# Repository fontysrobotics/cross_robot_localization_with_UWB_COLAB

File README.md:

# cross_robot_localization_with_UWB_COLAB

The new way to design large scale automation project is through the use of Autonomously Guided Vehicles (AGVs). They allow the connection of different workcells to have more flexibility and all this autonomously. This new technology brings a brandd new market with different companies competing to manufacture the best robot for a said application. This brings the costumers to a place where they have to go to different suppliers for the best AGVs based on their application. Incorporating AGVSs of different brands in the same automation process is a difficult task. While AGVs are good at navigating around a building and completing repetitive tasks, when faced with an unknown moving object such as another AGV they get into trouble. As the different brands cannot communicate this creates a serious issue.

## Project

The goal of the project is to make collaboration between AGVs of different brands possible using a relatively cheap solution. The main issue with collaboration is the lack of communication of crucial data. As the issue arises for navigation, the most important data to be shared between the AGVs is location. Localizing multi-vendor AGVs and sharing their location on the same delocalised system. This will allow the recognition of AGVs as obstacles and will leave room for future implementation of a task division control system. This delocalised communication system will achieve collaboration between the AGVs of various brands.

## Problem

The problem of the assignment is to create a delocalised communication system between the AGVs that can determine the position of each AGV. The localization system is built on the decawave UWB device. The principle of this device is to use the delay in Ultra Wide Band signals to measure distance between the devices on the same network. This localization system must be integrated with the AGVs. Each AGV must have a UWB device for localization which in some way has to be connected to a network of all other AGVs. The creation of this system is the problem of the assignment.

## Solution

In order to incorporate the UWB localization system with the AGV, a device titled Communication and Localization Add on Board or CoLAB was created as a solution. The CoLAB device handles the creation and connection of an AGV to the localization network as well as to the UWB network and the AGV. A CoLAB device is attached to each AGV along with two UWB devices that serve as a front and back tag for the positioning. Inside the CoLAb is a Raspberry pi that reads the positioning information from the two tags via UART. This information is processed to return location and orientation. The CoLAB publishes location, orientation and other useful information from the AGV config file as a message to a network which all AGVs are connected to. From this network AGVs scan and read messages of other AGVs and determine their location orientation and most important properties. This information is sent to the AGV and can be implemented for the software to recognize other AGVs as obstacles. Thus, solving the Communication and Localization issue between AGVs of different vendors. This system also opens the possibility to many more future solutions.

## Navigation of gitHub Page

Within the following the contents of the CoLAB gitHub page will be explained. The three main components the read me, repository and wiki will be highlighted.

* ### Read Me 
Within the read me the basic introduction to the project and problem happens. The products of the project thus to content of the gitHub page is also explained. Alongside this information the main credits to the page as well as a quick how to use guide can be found.

* ### Repository
The repository is where the final products of the project thus the content can be found. This is where the final designs and software can be downloaded from. All the research material used is also provided alongside the datasheets and explaining flow charts and diagrams. Some files to aid with system set up can also be found in the repository.

* ### Wiki
The wiki is where the design is given a further explanation. Each components of the system is given a page along with explanations to its design. Some pages elaborate on the system, validation or final conclusions. For navigation use the table of contents side bar on the right side of the page.

## How to use

Within the following a quick start guide will be given on how to set up the CoLAB system on your own AGV. It is Important to note that this guide will give a global layout and reference set up files, however some extra more in depth set up information might be found in the referenced files.

* ### How to initiate (loading code + connect)
In order to set up a system like the CoLAB first order all the components, print the parts and PCB. After this is completed there is a guide titled (start guide) in the depositor that is an assembly guide to the CoLAB. In this guide further information details how to set up a raspberry pi for the CoLAB as well.
Once the CoLAB is set up it is time to set up the UWB devices with the correct image. Only the tags on the AGV have to be set up

* ### How to set up (config)
It is very easy to use a CoLAB device. It is almost plug and play. There are a couple of things that need to be commpleted before use. A list of these can be found below. It is important to note that these steps must be repeated for each CoLAB device on each AGV.

1. Order all parts and assemble the device compoennets using the [guides](https://github.com/fontysrobotics/cross_robot_localization_with_UWB_COLAB/tree/main/PhysicalSystem/Assembly_documents)
1. Fill out [Configuration File](https://github.com/fontysrobotics/cross_robot_localization_with_UWB_COLAB/blob/main/Software/CoLAB_config.py) of AGV
1. Plug tags to CoLAB and Attach to AGV
1. Note down distance between tags in config file
1. Set up ports of tags using [set up guide](https://github.com/fontysrobotics/cross_robot_localization_with_UWB_COLAB/blob/main/UWB_Documentation/UWB_Setup_Guides/Use%20RaspberryPi%20terminal%20(1).docx)
1. The device must be connected to the network and it is ready to use

* ### End results
As an end reslut of running the code correctly, there are two important aspects taht happen. The communication code between all the connected AGVs is running and they are communicating their information to each other. The second thing is a visualziation software that is built into every AGV. This shows the AGVs around. This is the end result of code in a nutshell, the wiki explains further information of the exact communication and information passing through.

## Bibliography & Credits

This project was created as part of a Mechatronics university course for Fontys University of Applied Sciences with the involvement of the following parties:

### Created by
* Nicole Celine
* Arjan van der Heijden
* Mike Luiken
* Simeon Stoyanov
* Pascal Dinjens
* Long Nguyen
* Ryan Muhammad
* Benedek Papp

### Mentorship and Project Ownership
* Pablo Negrete Rubio
* Sjriek Alers

Throughout the project the following sources were used as guidence, inspiration and technical details:

### Sources

* EEAdi, et al. “Using DWM1001 API on Raspberry Pi and PySerial.” Decawave Tech Forum, 8 Dec. 2019, [decaforum.decawave.com/t/using-dwm1001-api-on-raspberry-pi-and-pyserial/6567]( decaforum.decawave.com/t/using-dwm1001-api-on-raspberry-pi-and-pyserial/6567). 

* Robots, Mobile Industrial. “Please Select Language.” MiR100™ | Mobile Industrial Robots, [www.mobile-industrial-robots.com/en/solutions/robots/mir100/]( www.mobile-industrial-robots.com/en/solutions/robots/mir100/). 

* “The Standard for IoT Messaging.” MQTT, [mqtt.org/]( mqtt.org/).

* Eclipse Mosquitto, 8 Jan. 2018, [mosquitto.org/]( mosquitto.org/.). 

* Craggs, Ian. “Eclipse Paho: The Eclipse Foundation.” Enabling Open Innovation & Collaboration, [www.eclipse.org/paho/]( www.eclipse.org/paho/). 

* “Visualization with Python¶.” Matplotlib, [matplotlib.org/]( matplotlib.org/). 

* “Home.” Decawave, 29 May 2019, [decawave.com/](decawave.com/). 

* Apichet Garaipoom I love the electronic circuits. I will collect a lot of circuit electronics to teach my son and are useful for everyone., et al. “LM2596 Circuit Voltage Regulator and LM2673 Datasheet.” ElecCircuit.com, 19 July 2020, [www.eleccircuit.com/regulator-switching-dc-to-dc-step-down-voltage-with-lm2596/]( www.eleccircuit.com/regulator-switching-dc-to-dc-step-down-voltage-with-lm2596/.). 

* “LTC Debuts LTC4060 NiMH/NiCd Battery Charger - New Industry Products.” EEPower, [eepower.com/new-industry-products/ltc-debuts-ltc4060-nimhnicd-battery-charger/#]( eepower.com/new-industry-products/ltc-debuts-ltc4060-nimhnicd-battery-charger/#). 

* “Dual 4A Ideal Diodes with Adjustable Current Limit.” Datasheet, Linear Technology Co., [datasheet.datasheetarchive.com/originals/distributors/Datasheets-SFU1/DSASFU10008413.pdf]( datasheet.datasheetarchive.com/originals/distributors/Datasheets-SFU1/DSASFU10008413.pdf). 

* Zach-Goh. “Zach-Goh/Omron_LD_ROS_Package.” GitHub, [github.com/zach-goh/Omron_LD_ROS_Package](github.com/zach-goh/Omron_LD_ROS_Package). 

* “OMRON Industrial Automation.” OMRON, [www.ia.omron.com/]( www.ia.omron.com/). 

* “BU-203: Nickel-Based Batteries.” Nickel-Based Batteries Information – Battery University, [batteryuniversity.com/learn/article/nickel_based_batteries](batteryuniversity.com/learn/article/nickel_based_batteries).

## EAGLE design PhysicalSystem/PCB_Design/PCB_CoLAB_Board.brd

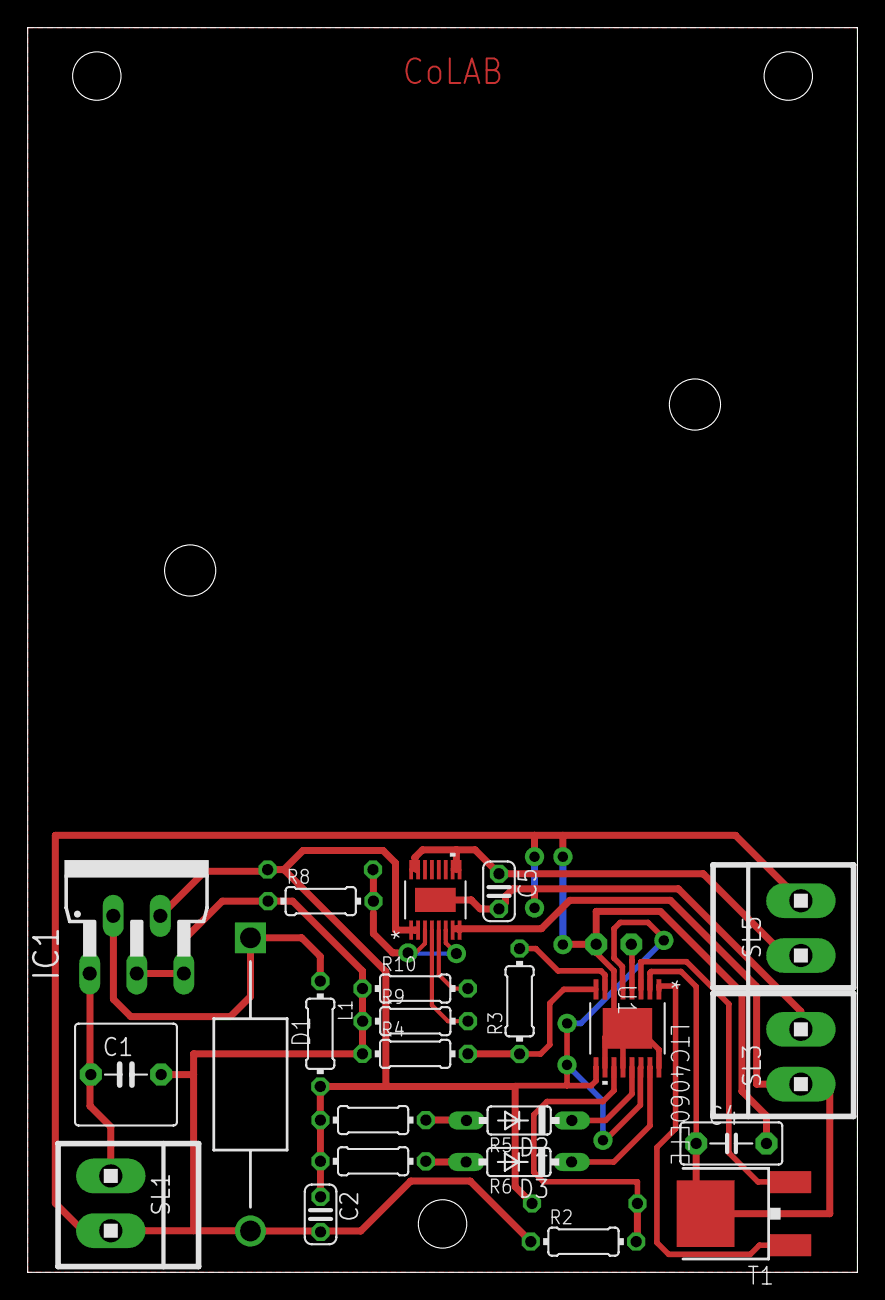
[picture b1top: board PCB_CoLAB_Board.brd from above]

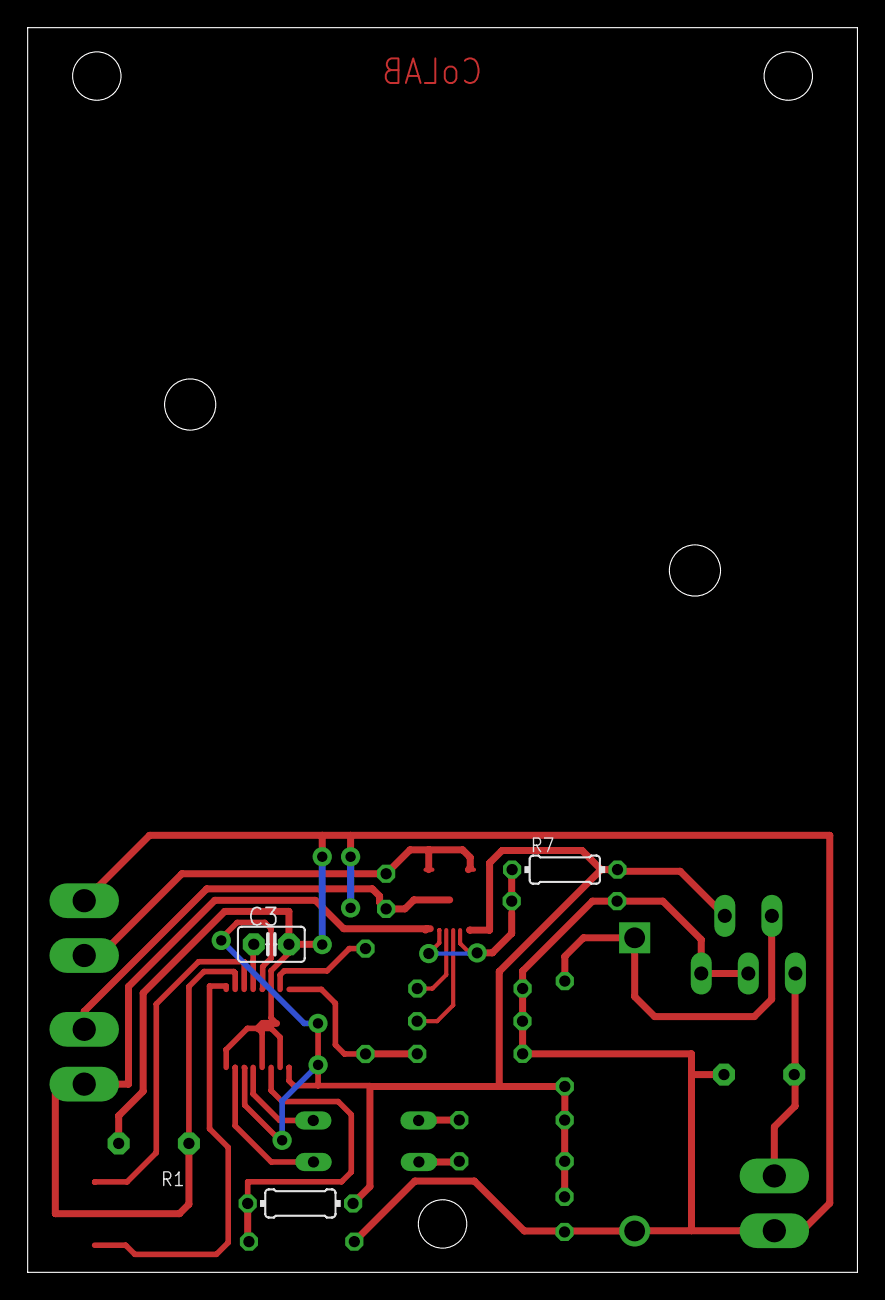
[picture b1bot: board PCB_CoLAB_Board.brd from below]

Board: 2 copper layers, 60.0 x 90.0 mm, 26 parts (3 on the bottom side), 18 nets.

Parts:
C1: C5B7.2
C2, C5: C025-024X044
C3: C2.5-2
C4: C5B3
D1: 1N5822; DIOAD2120W130L950D530P
D2, D3: 1N4148DO35-7; DO35-7
IC1: LM2596T; T05D
L1: 0204/7
R1, R2, R3, R4, R5, R6, R7, R8, R9, R10: 0204/7
SL1, SL3, SL5: 1X2MTA
T1: MJD32; DPAK
U1: LTC4060EFE; TSSOP-16_FE/BC_LIT
U2: LTC4415EMSEPBF; MSOP-16_MSE

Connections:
GND: C1.2, C2.2, C3.2, C4.2, C5.2, D1.A, IC1.3, IC1.5, R2.1, R4.1, R8.1, R9.1, R10.1, SL1.1, SL3.1, SL5.1, U1.6, U1.10, U1.12, U1.16, U1.EPAD, U2.17
unnamed: R3.2, U1.7
unnamed: C1.1, IC1.1, SL1.2
unnamed: D1.C, IC1.2, L1.1
unnamed: R1.1, R2.2, U1.11
unnamed: R7.1, R8.2, U2.3, U2.6
unnamed: R3.1, R4.2, U1.8
unnamed: T1.3, U1.3
unnamed: T1.1, U1.1
unnamed: C2.1, IC1.4, L1.2, R1.2, R5.2, R6.2, R7.2, U1.5, U1.9, U1.14, U2.1
unnamed: C3.1, U1.4
unnamed: D2.A, R5.1
unnamed: D2.C, U1.13
unnamed: D3.C, U1.15
unnamed: D3.A, R6.1
unnamed: C4.1, SL3.2, T1.4, U1.2, U2.7, U2.8
unnamed: R10.2, U2.5
unnamed: C5.1, SL5.2, U2.9, U2.10, U2.15, U2.16

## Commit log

2021-01-25 Create 1
2021-01-25 Create UWB_testing
2021-01-27 Create Downloaded
2021-01-31 Create Omron_image
2021-02-01 Create LICENSE
2021-02-01 Create a
